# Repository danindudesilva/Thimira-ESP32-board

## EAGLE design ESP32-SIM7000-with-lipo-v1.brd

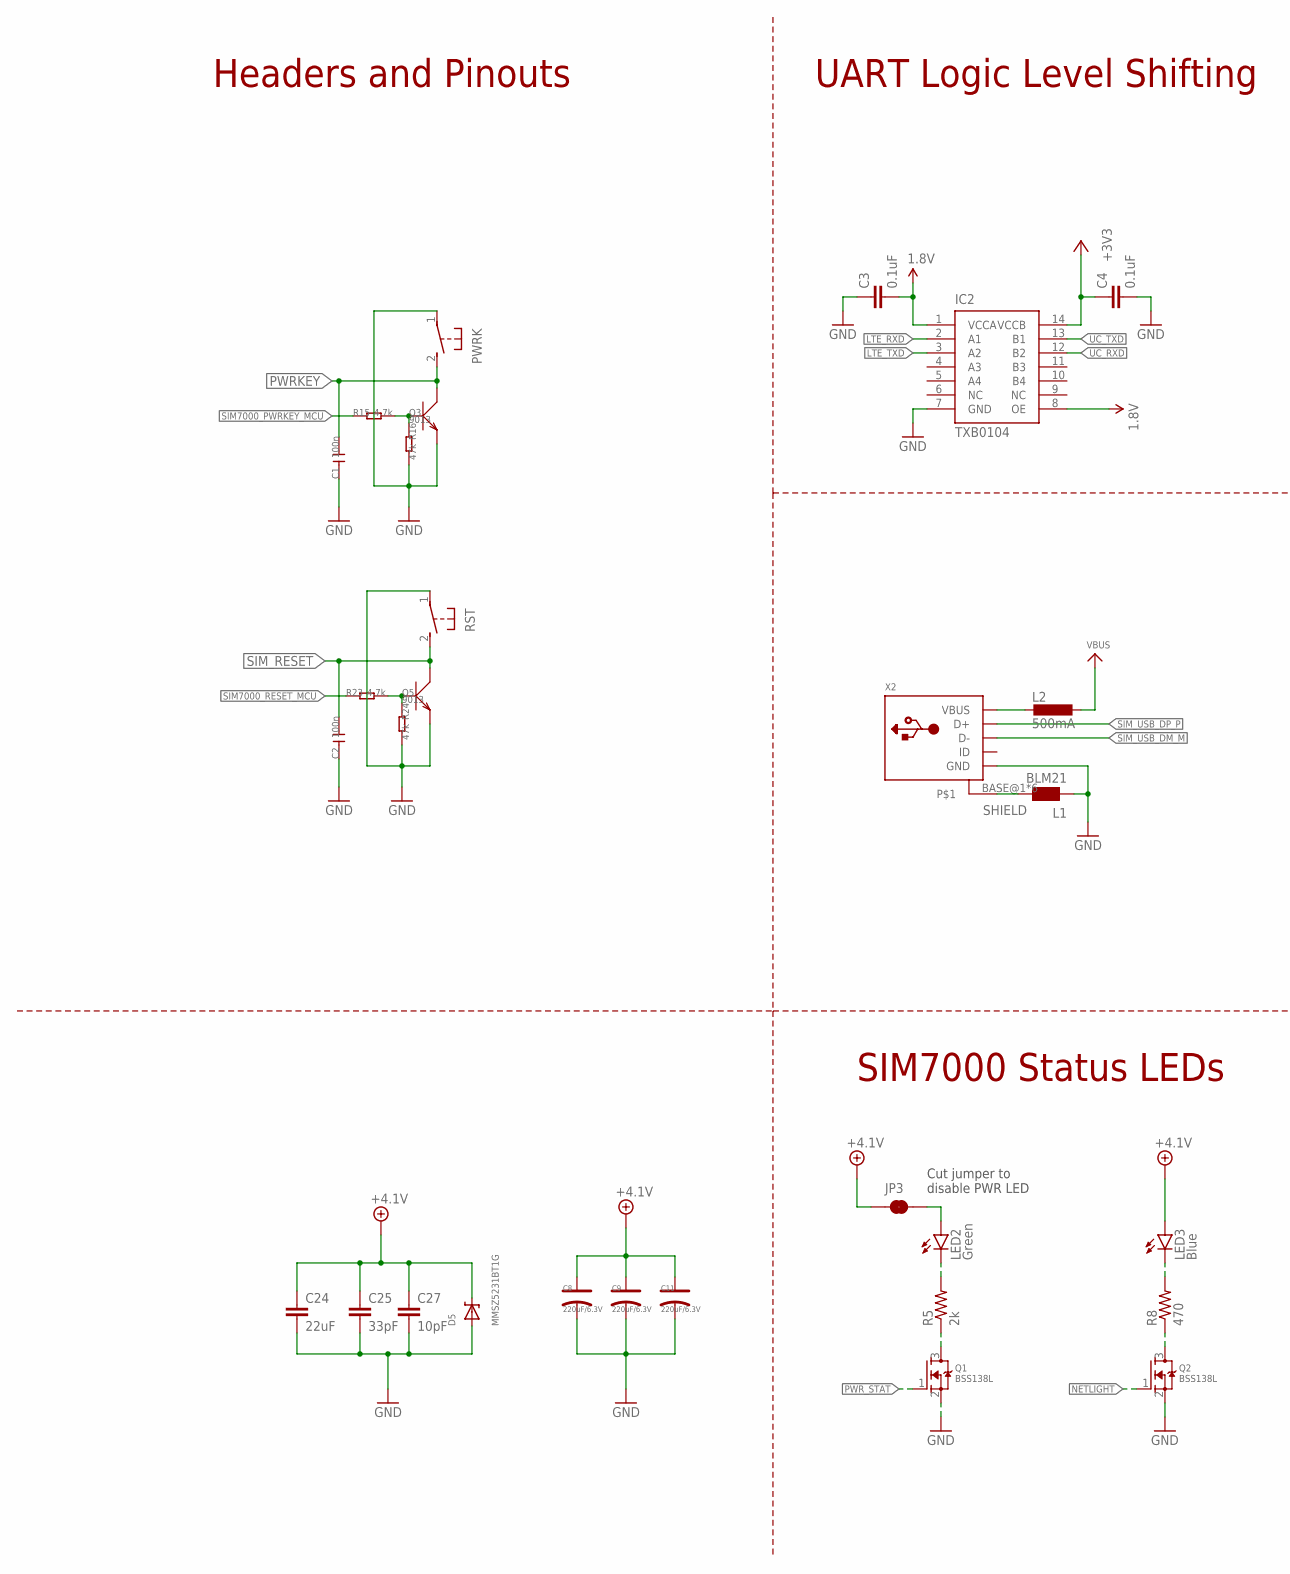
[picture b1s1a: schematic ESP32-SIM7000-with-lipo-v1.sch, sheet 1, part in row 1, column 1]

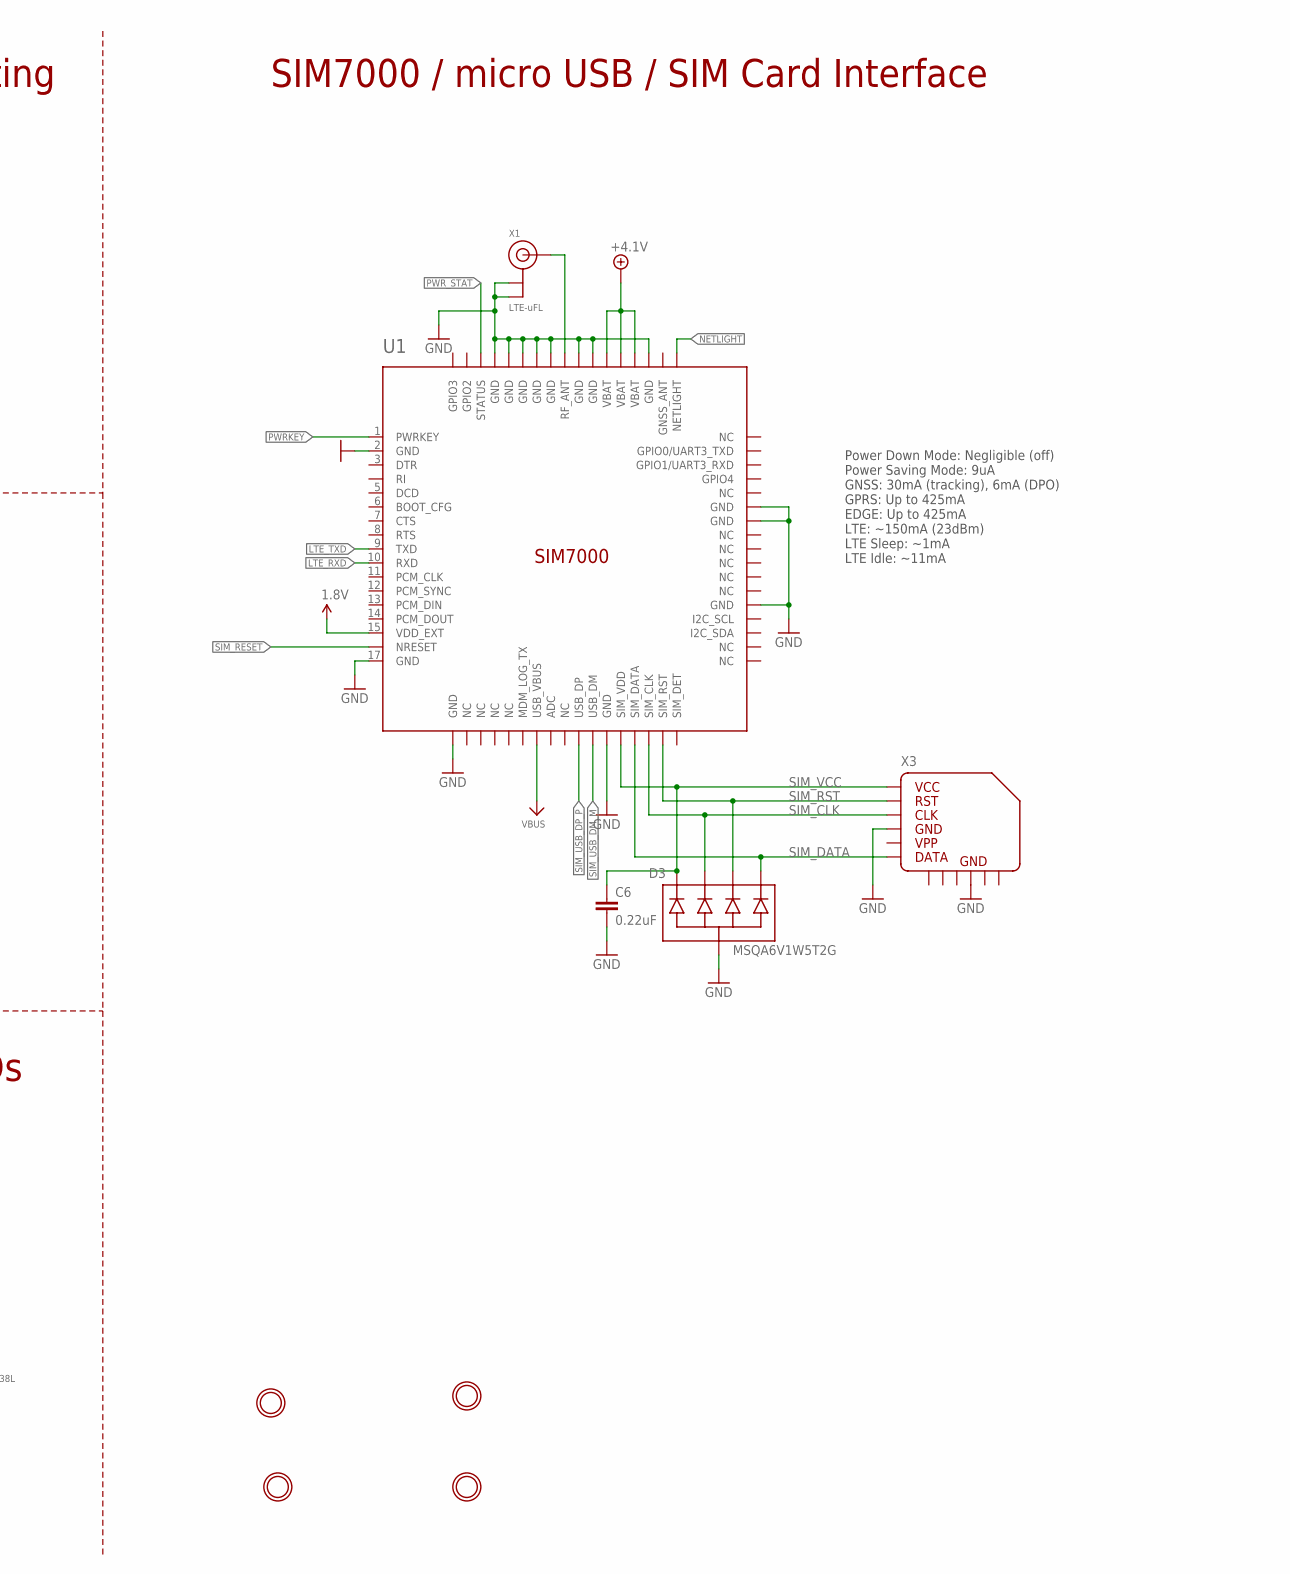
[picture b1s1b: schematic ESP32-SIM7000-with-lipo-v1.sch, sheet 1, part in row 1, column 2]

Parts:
$H1, $H2, $H3, $H4: MOUNTINGHOLE3.0THIN; MOUNTINGHOLE_3.0_PLATEDTHIN
C1, C2: 100n; 0805
C3, C4: 0.1uF; 0603-CAP-MARKED
C6: 0.22uF; 0603-CAP-MARKED
C8, C9, C11: 220uF/6.3V; AVX_C
C24: 22uF; 0805
C25: 33pF; 0805
C27: 10pF; 0805
D3: MSQA6V1W5T2G; SOT-353
D5: MMSZ5231BT1G; SOD-123
IC2: TXB0104; SOIC-14
JP3: JUMPER-SMT_2_NC_TRACE_SILK; SMT-JUMPER_2_NC_TRACE_SILK
L1: BLM21; 0805
L2: 500mA; L1812
LED2: Green; LED-0603-MARKED
LED3: Blue; LED-0603-MARKED
PWRK: DTSM-3
Q1, Q2: BSS138L; SOT23-3
Q3, Q5: 9013; SOT23
R5: 2k; 0603-RES-MARKED
R8: 470; 0603-RES-MARKED
R15, R23: 4.7k; 0805
R16, R24: 47k; 0805
RST: DTSM-3
U1: SIM7000
X1: LTE-uFL; U.FL
X2: USB_MICRO_20329_V2; 4UCONN_20329_V2
X3: MICROSIM_SOCKET_PUSH-PULL

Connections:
1.8V: C3.2, IC2.1 (VCCA), IC2.8 (OE), U1.15 (VDD_EXT)
+3V3: C4.1, IC2.14 (VCCB); also elsewhere on the board
+4.1V: C8.+, C9.+, C11.+, C24.1, C25.1, C27.1, D5.C, JP3.1, LED3.A, U1.55 (VBAT), U1.56 (VBAT), U1.57 (VBAT); also elsewhere on the board
GND: C1.1, C2.1, C3.1, C4.2, C6.2, C8.-, C9.-, C11.-, C24.2, C25.2, C27.2, D3.2 (COM), D5.A, IC2.7 (GND), L1.1, PWRK.1, Q1.2 (S), Q2.2 (S), Q3.2 (E), Q5.2 (E), R16.2, R24.2, RST.1, U1.2 (GND), U1.17 (GND), U1.18 (GND), U1.29 (GND), U1.39 (GND), U1.45 (GND), U1.46 (GND), U1.54 (GND), U1.58 (GND), U1.59 (GND), U1.61 (GND), U1.62 (GND), U1.63 (GND), U1.64 (GND), U1.65 (GND), X1.1 (GND), X1.2 (GND), X2.GND, X3.C5, X3.GND@1 (GND), X3.GND@2 (GND), X3.GND@3 (GND), X3.GND@4 (GND), X3.GND@5 (GND), X3.GND@6 (GND); also elsewhere on the board
LTE_RXD: IC2.2 (A1), U1.10 (RXD)
LTE_TXD: IC2.3 (A2), U1.9 (TXD)
unnamed: Q1.3 (D), R5.1
unnamed: LED2.C, R5.2
unnamed: Q2.3 (D), R8.1
unnamed: LED3.C, R8.2
unnamed: JP3.2, LED2.A
unnamed: Q5.1 (B), R23.2, R24.1
unnamed: L2.2, X2.VBUS
unnamed: Q3.1 (B), R15.2, R16.1
NETLIGHT: Q2.1 (G), U1.52 (NETLIGHT)
PWRKEY: C1.2, PWRK.2, Q3.3 (C), U1.1 (PWRKEY)
PWR_STAT: Q1.1 (G), U1.66 (STATUS)
RF_ANT: U1.60 (RF_ANT), X1.3 (SIGNAL)
SHIELD: L1.2, X2.BASE@1, X2.BASE@2, X2.SPRT@1, X2.SPRT@2, X2.SPRT@3, X2.SPRT@4
SIM7000_PWRKEY_MCU: R15.1; also elsewhere on the board
SIM7000_RESET_MCU: R23.1; also elsewhere on the board
SIM_CLK: D3.3 (2), U1.32 (SIM_CLK), X3.C3
SIM_DATA: D3.5 (4), U1.31 (SIM_DATA), X3.C7
SIM_RESET: C2.2, Q5.3 (C), RST.2, U1.16 (NRESET)
SIM_RST: D3.4 (3), U1.33 (SIM_RST), X3.C2
SIM_USB_DM_M: U1.28 (USB_DM), X2.D-
SIM_USB_DP_P: U1.27 (USB_DP), X2.D+
SIM_VCC: C6.1, D3.1, U1.30 (SIM_VDD), X3.C1
UC_RXD: IC2.12 (B2); also elsewhere on the board
UC_TXD: IC2.13 (B1); also elsewhere on the board
VBUS: L2.1, U1.24 (USB_VBUS); also elsewhere on the board

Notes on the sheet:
SIM7000 / micro USB / SIM Card Interface
Headers and Pinouts
UART Logic Level Shifting
SIM7000 Status LEDs
Cut jumper to disable PWR LED
Power Down Mode: Negligible (off) Power Saving Mode: 9uA GNSS: 30mA (tracking), 6mA (DPO) GPRS: Up to 425mA EDGE: Up to 425mA LTE: ~150mA (23dBm) LTE Sleep: ~1mA LTE Idle: ~11mA

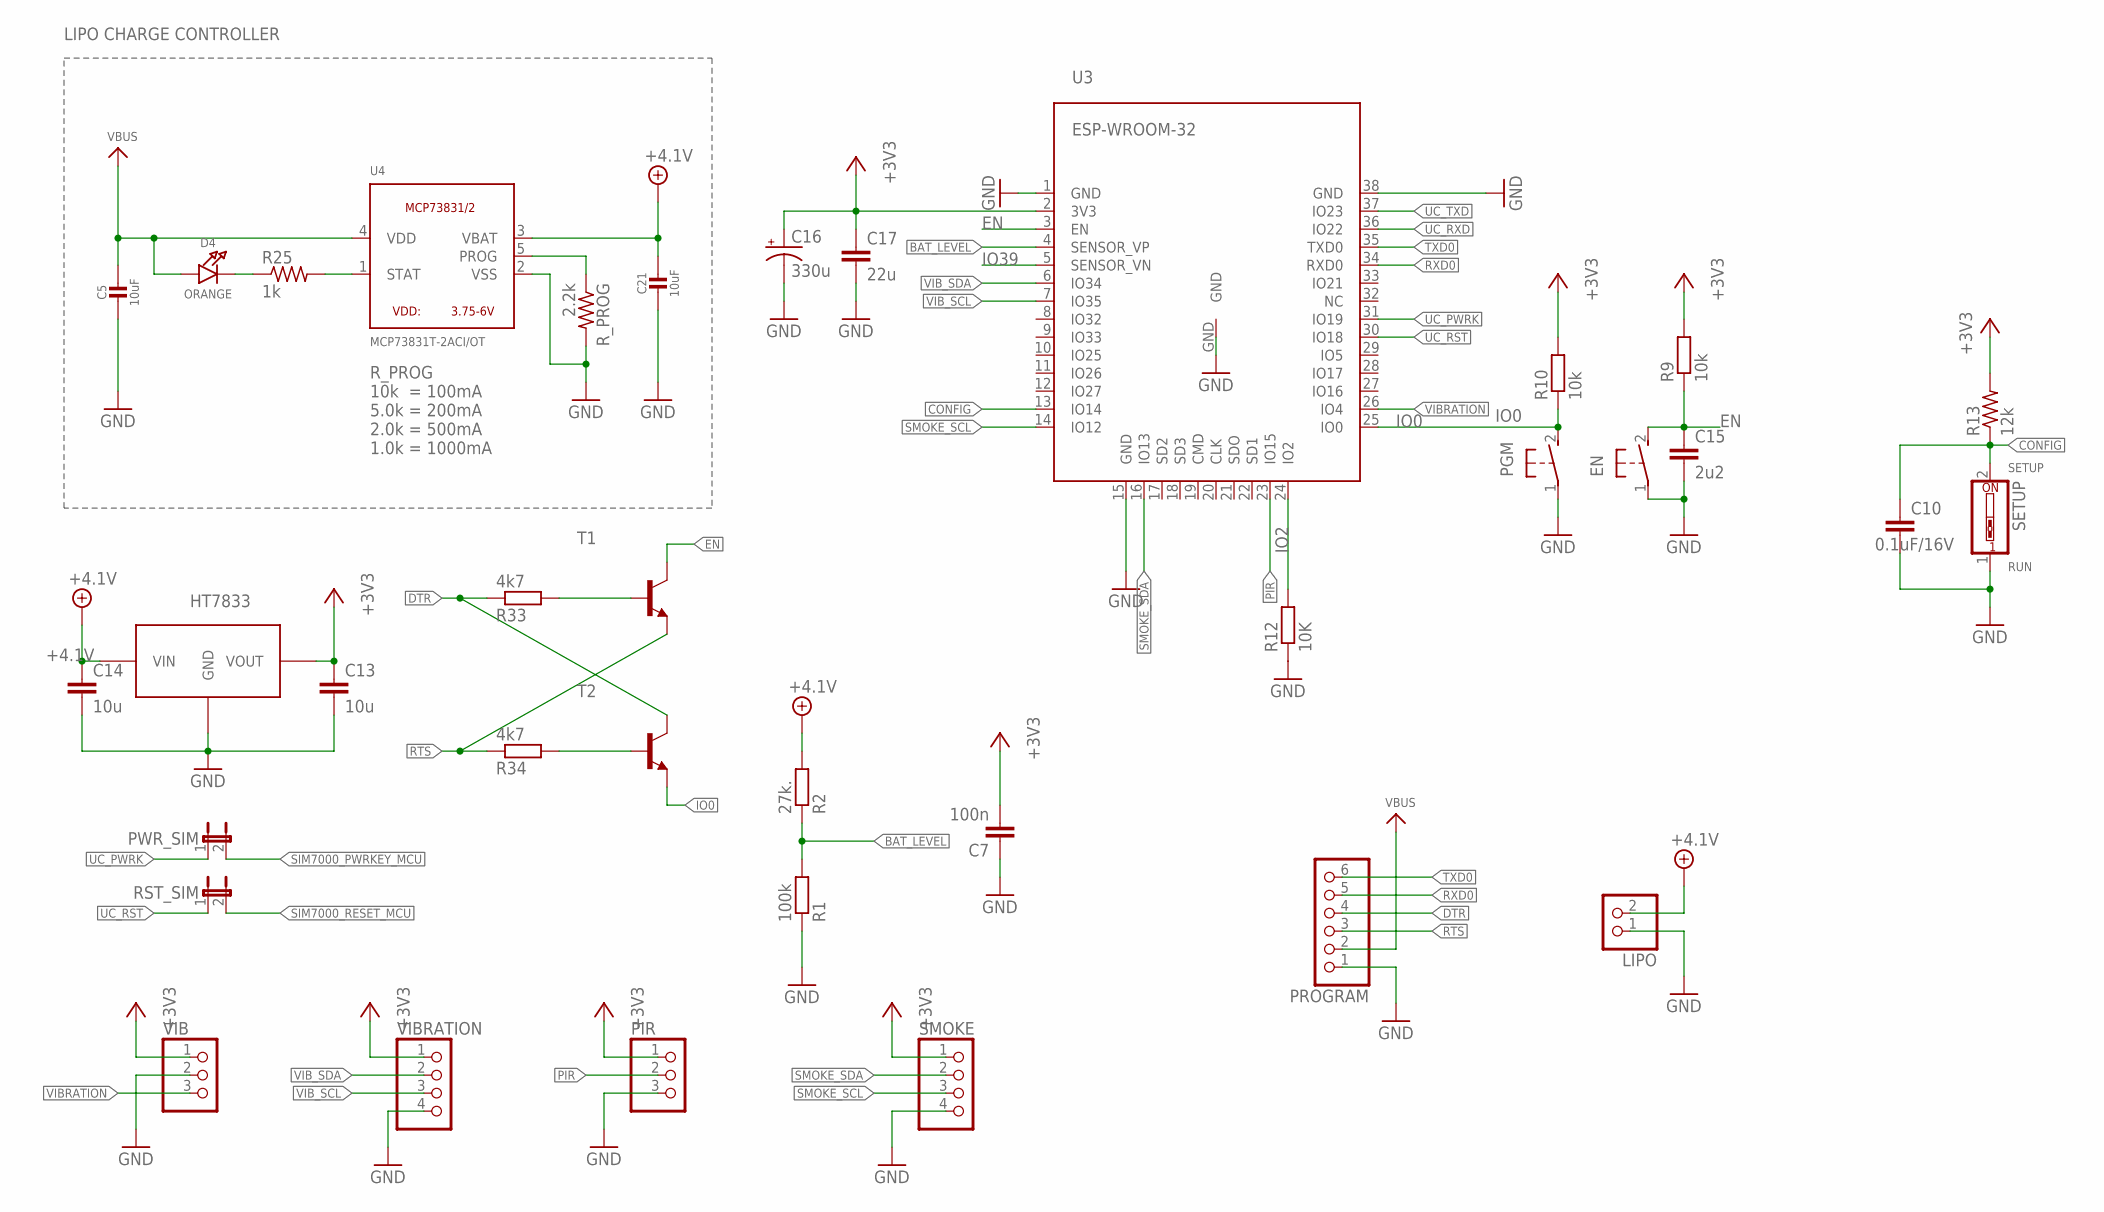
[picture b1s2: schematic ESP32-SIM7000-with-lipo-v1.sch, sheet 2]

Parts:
C5, C21: 10uF; _0805
C7: 100n; C0805
C10: 0.1uF/16V; C0805K
C13, C14: 10u; C0603
C15: 2u2; C0603
C16: 330u; VISHAY_C
C17: 22u; 0805
D4: ORANGE; CHIPLED_0805
EN: DTSM-3
LIPO: PINHD-1X2; 1X02
PGM: DTSM-3
PIR: PINHD-1X3; 1X03
PROGRAM: PINHD-1X6; 1X06
PWR_SIM: SPARKFUN-PASSIVES_JUMPER-PTH-2-NC; SPARKFUN-PASSIVES_PTH-JUMPER-NC_BOTTOM_NO_SILK
R1: 100k; R0805
R2: 27k.; R0805
R9, R10: 10k; R0603@1
R12: 10K; R0603@1
R13: 12k; M0805
R25: 1k; M0805
R33, R34: 4k7; R0805
RST_SIM: SPARKFUN-PASSIVES_JUMPER-PTH-2-NC; SPARKFUN-PASSIVES_PTH-JUMPER-NC_BOTTOM_NO_SILK
R_PROG: 2.2k; M0805
SETUP: SW_DIP-1; EDG-01
SMOKE: PINHD-1X4; 1X04
T1, T2: MMBT3904LT1-NPN-SOT23-BEC; SOT23-BEC
U3: ESP-WROOM-32
U4: MCP73831T-2ACI/OT; SOT23-5
U$1: HT7833; SOT89
VIB: PINHD-1X3; 1X03
VIBRATION: PINHD-1X4; 1X04

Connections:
+3V3: C7.2, C13.1, C16.+, C17.1, PIR.1, R9.2, R10.2, R13.2, SMOKE.1, U3.2 (3V3), U$1.VOUT, VIB.1, VIBRATION.1; also elsewhere on the board
+4.1V: C14.1, C21.1, LIPO.2, R2.2, U4.3 (VBAT), U$1.VIN; also elsewhere on the board
BAT_LEVEL: R1.2, R2.1, U3.4 (SENSOR_VP)
CONFIG: C10.1, R13.1, SETUP.2, U3.13 (IO14)
DTR: PROGRAM.4, R33.1, T2.C
EN: C15.1, EN.2, R9.1, T1.C, U3.3 (EN)
GND: C5.2, C7.1, C10.2, C13.2, C14.2, C15.2, C16.-, C17.2, C21.2, EN.1, LIPO.1, PGM.1, PIR.3, PROGRAM.1, R1.1, R12.1, R_PROG.2, SETUP.1, SMOKE.4, U3.1 (GND), U3.15 (GND), U3.38 (GND), U3.GND, U4.2 (VSS), U$1.GND, VIB.2, VIBRATION.4; also elsewhere on the board
IO0: PGM.2, R10.1, T2.E, U3.25 (IO0)
IO2: R12.2, U3.24 (IO2)
IO39: U3.5 (SENSOR_VN)
unnamed: D4.C, R25.1
unnamed: R25.2, U4.1 (STAT)
unnamed: R_PROG.1, U4.5 (PROG)
unnamed: R33.2, T1.B
unnamed: R34.2, T2.B
PIR: PIR.2, U3.23 (IO15)
RTS: PROGRAM.3, R34.1, T1.E
RXD0: PROGRAM.5, U3.34 (RXD0)
SIM7000_PWRKEY_MCU: PWR_SIM.2; also elsewhere on the board
SIM7000_RESET_MCU: RST_SIM.2; also elsewhere on the board
SMOKE_SCL: SMOKE.3, U3.14 (IO12)
SMOKE_SDA: SMOKE.2, U3.16 (IO13)
TXD0: PROGRAM.6, U3.35 (TXD0)
UC_PWRK: PWR_SIM.1, U3.31 (IO19)
UC_RST: RST_SIM.1, U3.30 (IO18)
UC_RXD: U3.36 (IO22); also elsewhere on the board
UC_TXD: U3.37 (IO23); also elsewhere on the board
VBUS: C5.1, D4.A, PROGRAM.2, U4.4 (VDD); also elsewhere on the board
VIBRATION: U3.26 (IO4), VIB.3
VIB_SCL: U3.7 (IO35), VIBRATION.3
VIB_SDA: U3.6 (IO34), VIBRATION.2

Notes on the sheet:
R_PROG 10k = 100mA 5.0k = 200mA 2.0k = 500mA 1.0k = 1000mA
LIPO CHARGE CONTROLLER
RUN
SETUP

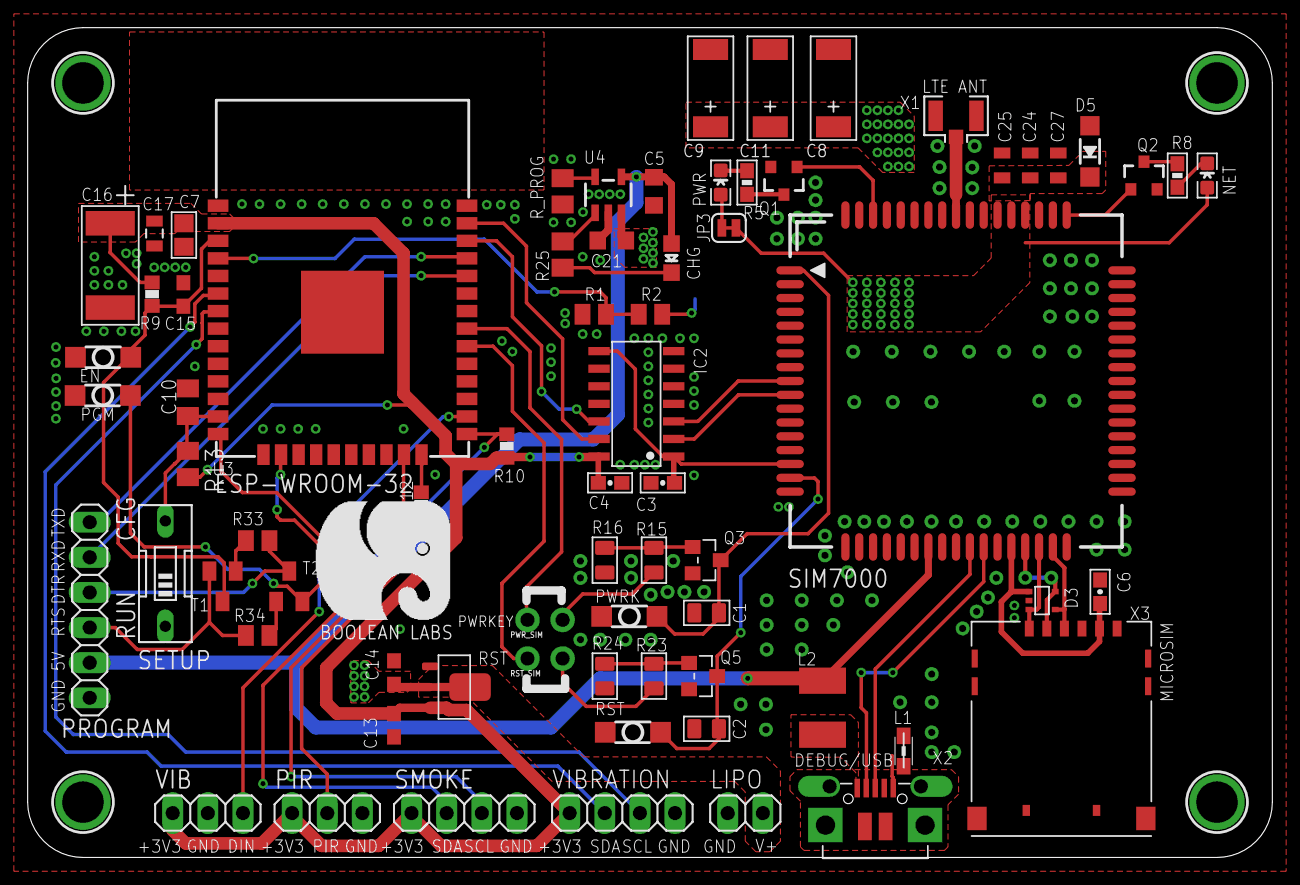
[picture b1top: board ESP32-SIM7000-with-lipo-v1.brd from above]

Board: 2 copper layers, 90.0 x 60.0 mm, 75 parts (0 on the bottom side), 53 nets.

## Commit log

2020-05-31 route remaining traces
2020-05-31 Naming components
2020-06-01 adds vias and completes DRC
2020-06-01 Schematic frames changes
2020-06-04 Logo and config switch
2020-06-07 Adds TVS and small caps to Vbat pins
2020-06-07 Adds power caps
2020-06-07 Adds some vias
2020-06-07 change caps package

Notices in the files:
parts and their libraries:
SparkFun-Passives: Licensing: Creative Commons ShareAlike 4.0 International - https://creativecommons.org/licenses/by-sa/4.0
SparkFun-Capacitors: Licensing: CC v3.0 Share-Alike You are welcome to use this library for commercial purposes.
